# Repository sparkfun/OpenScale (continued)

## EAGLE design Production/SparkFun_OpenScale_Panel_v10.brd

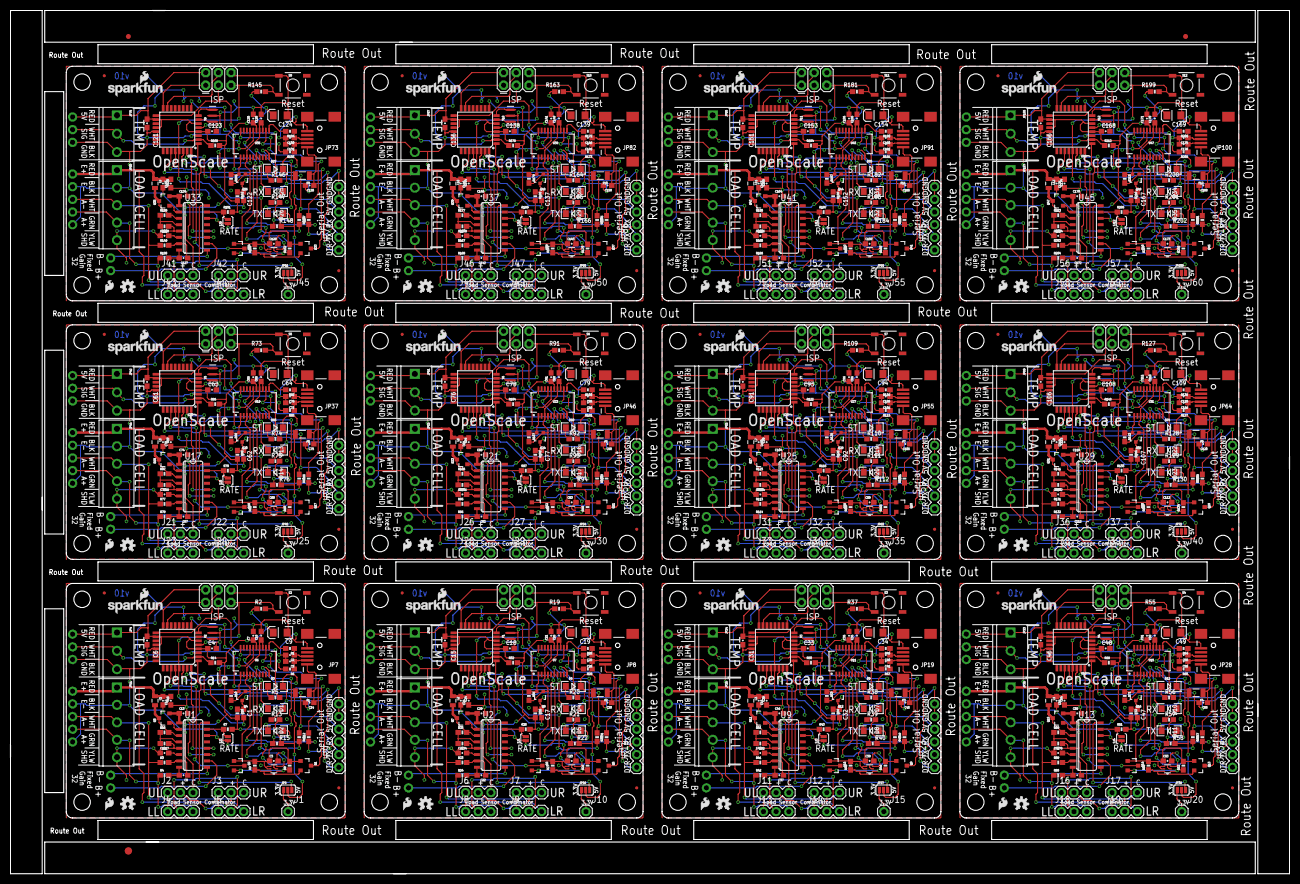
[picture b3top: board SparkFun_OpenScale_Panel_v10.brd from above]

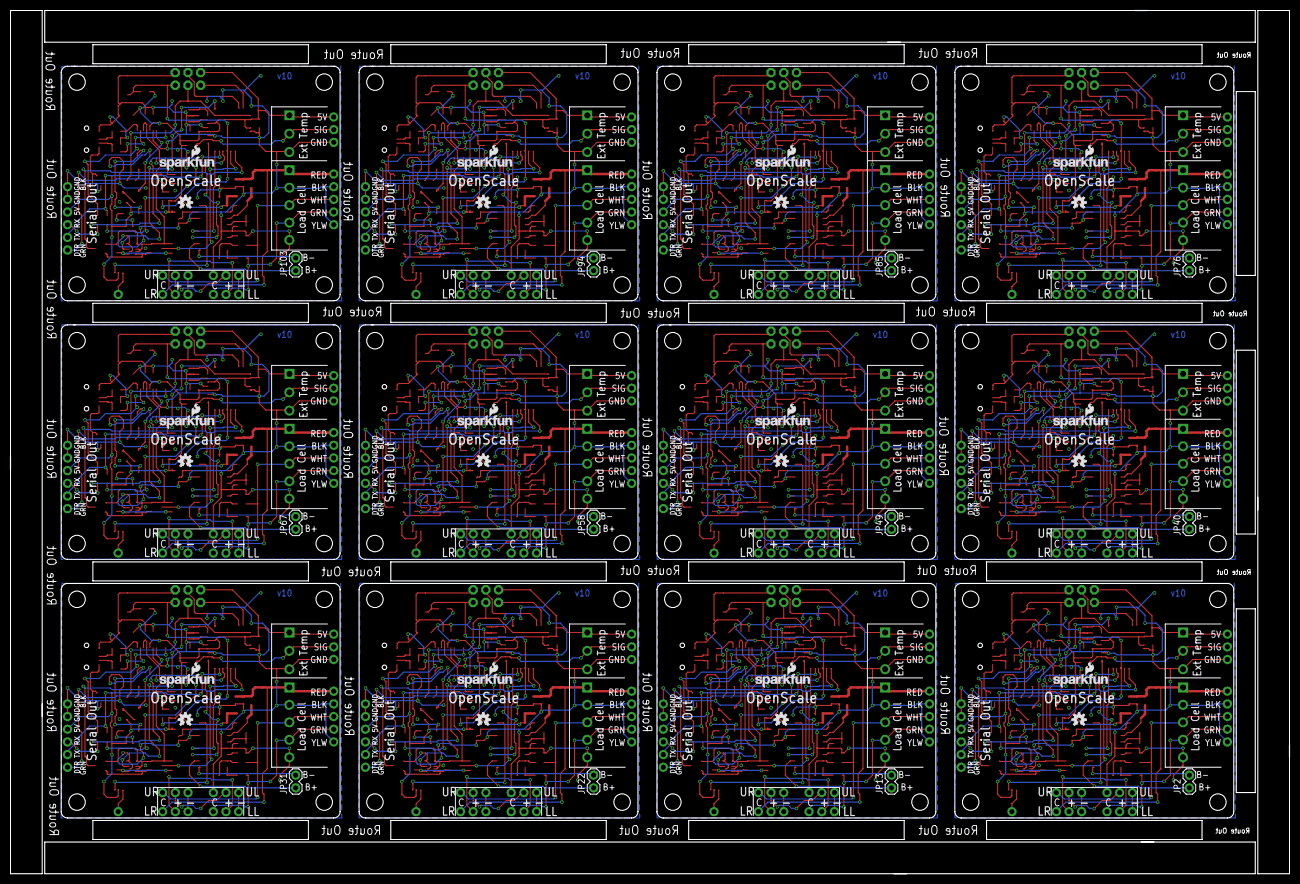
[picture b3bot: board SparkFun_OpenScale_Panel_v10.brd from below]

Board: 2 copper layers, 256.3 x 173.0 mm, 891 parts (48 on the bottom side), 612 nets.

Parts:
C1, C3, C6, C7, C8, C10, C11, C14, C15, C16, C17, C20, C21, C22, C23, C24, C27, C30, C31, C32, C35, C36, C37, C38, C39, C42, C45, C46, C47, C50, C51, C52, C53, C54, C57, C60, C61, C62, C65, C66, C67, C68, C69, C72, C75, C76, C77, C80, C81, C82, C83, C84, C87, C90, C91, C92, C95, C96, C97, C98, C99, C102, C105, C106, C107, C110, C111, C112, C113, C114, C117, C120, C121, C122, C125, C126, C127, C128, C129, C132, C135, C136, C137, C140, C141, C142, C143, C144, C147, C150, C151, C152, C155, C156, C157, C158, C159, C162, C165, C166, C167, C170, C171, C172, C173, C174, C177, C180: 0.1uF; 0603-CAP
C2, C5, C25, C26, C40, C41, C55, C56, C70, C71, C85, C86, C100, C101, C115, C116, C130, C131, C145, C146, C160, C161, C175, C176: 47pF; 0603-CAP
C4, C12, C13, C18, C28, C29, C33, C43, C44, C48, C58, C59, C63, C73, C74, C78, C88, C89, C93, C103, C104, C108, C118, C119, C123, C133, C134, C138, C148, C149, C153, C163, C164, C168, C178, C179: 1.0uF; 0603-CAP
C9, C19, C34, C49, C64, C79, C94, C109, C124, C139, C154, C169: 10uF; EIA3216
D1, D4, D7, D10, D13, D16, D19, D22, D25, D28, D31, D34: Yellow; LED-1206
D2, D5, D8, D11, D14, D17, D20, D23, D26, D29, D32, D35: GREEN; LED-1206
D3, D6, D9, D12, D15, D18, D21, D24, D27, D30, D33, D36: BLUE; LED-1206
E$1: FIDUCIAL-1.5X3
E$7, E$8: FIDUCIAL-1X2
F1, F2, F3, F4, F5, F6, F7, F8, F9, F10, F11, F12: PTCSMD; PTC-1206
FID1, FID2, FID3, FID4, FID5, FID6, FID7, FID8, FID9, FID10, FID11, FID12, FID13, FID14, FID15, FID16, FID17, FID18, FID19, FID20, FID21, FID22, FID23, FID24: FIDUCIALUFIDUCIAL; MICRO-FIDUCIAL
J1, J10, J15, J20, J25, J30, J35, J40, J45, J50, J55, J60: 3.3V; 1X01
J2, J6, J11, J16, J21, J26, J31, J36, J41, J46, J51, J56: UL; 1X03
J3, J7, J12, J17, J22, J27, J32, J37, J42, J47, J52, J57: UR; 1X03
J4, J8, J13, J18, J23, J28, J33, J38, J43, J48, J53, J58: LL; 1X03
J5, J9, J14, J19, J24, J29, J34, J39, J44, J49, J54, J59: LR; 1X03
JP1, JP12, JP21, JP30, JP39, JP48, JP57, JP66, JP75, JP84, JP93, JP102: Temp; 1X03_NO_SILK
JP2, JP13, JP22, JP31, JP40, JP49, JP58, JP67, JP76, JP85, JP94, JP103: Fixed Gain 32; 1X02
JP3, JP16, JP25, JP34, JP43, JP52, JP61, JP70, JP79, JP88, JP97, JP106: Load; 1X05_NO_SILK
JP4, JP15, JP24, JP33, JP42, JP51, JP60, JP69, JP78, JP87, JP96, JP105: Screw; SCREWTERMINAL-3.5MM-3_LOCK.007S
JP5, JP10, JP20, JP29, JP38, JP47, JP56, JP65, JP74, JP83, JP92, JP101: AVR_PRG; 2X3
JP6, JP18, JP27, JP36, JP45, JP54, JP63, JP72, JP81, JP90, JP99, JP108: JUMPER-PAD-3-2OF3_NC_BY_PASTE; PAD-JUMPER-3-2OF3_NC_BY_PASTE_YES_SILK_FULL_BOX
JP7, JP8, JP19, JP28, JP37, JP46, JP55, JP64, JP73, JP82, JP91, JP100: USBSMD; USB-MINIB
JP9, JP14, JP23, JP32, JP41, JP50, JP59, JP68, JP77, JP86, JP95, JP104: FTDI_BASIC
JP11, JP17, JP26, JP35, JP44, JP53, JP62, JP71, JP80, JP89, JP98, JP107: Screw Terminals; SCREWTERMINAL-3.5MM-5
L1, L2, L3, L4, L5, L6, L7, L8, L9, L10, L11, L12: 3.3uH; 0805
LOGO1, LOGO4, LOGO7, LOGO9, LOGO12, LOGO14, LOGO17, LOGO19, LOGO22, LOGO24, LOGO27, LOGO29, LOGO32, LOGO34, LOGO37, LOGO39, LOGO42, LOGO44, LOGO47, LOGO49, LOGO52, LOGO54, LOGO57, LOGO59: SFE_LOGO_NAME_FLAME.1_INCH; SFE_LOGO_NAME_FLAME_.1
LOGO2, LOGO5, LOGO6, LOGO10, LOGO11, LOGO15, LOGO16, LOGO20, LOGO21, LOGO25, LOGO26, LOGO30, LOGO31, LOGO35, LOGO36, LOGO40, LOGO41, LOGO45, LOGO46, LOGO50, LOGO51, LOGO55, LOGO56, LOGO60: OSHW-LOGOS; OSHW-LOGO-S
LOGO3, LOGO8, LOGO13, LOGO18, LOGO23, LOGO28, LOGO33, LOGO38, LOGO43, LOGO48, LOGO53, LOGO58: SFE_LOGO_FLAME.1_INCH; SFE_LOGO_FLAME_.1
Q1, Q2, Q5, Q6, Q9, Q10, Q13, Q14, Q17, Q18, Q21, Q22, Q25, Q26, Q29, Q30, Q33, Q34, Q37, Q38, Q41, Q42, Q45, Q46: 200mA/50V; SOT23-3
Q3, Q7, Q11, Q15, Q19, Q23, Q27, Q31, Q35, Q39, Q43, Q47: MMBT4403; SOT23-3
Q4, Q8, Q12, Q16, Q20, Q24, Q28, Q32, Q36, Q40, Q44, Q48: MOSFET-NCHANNEL2N7002PW; SOT323
R1, R6, R28, R29, R46, R47, R64, R65, R82, R83, R100, R101, R118, R119, R136, R137, R154, R155, R172, R173, R190, R191, R208, R209: 27; 0603
R2, R7, R10, R18, R19, R25, R35, R36, R37, R43, R53, R54, R55, R61, R71, R72, R73, R79, R89, R90, R91, R97, R107, R108, R109, R115, R125, R126, R127, R133, R143, R144, R145, R151, R161, R162, R163, R169, R179, R180, R181, R187, R197, R198, R199, R205, R215, R216: 10K; 0603-RES
R3, R4, R23, R24, R41, R42, R59, R60, R77, R78, R95, R96, R113, R114, R131, R132, R149, R150, R167, R168, R185, R186, R203, R204: 100; 0603-RES
R5, R11, R12, R13, R15, R20, R21, R22, R30, R31, R38, R39, R40, R48, R49, R56, R57, R58, R66, R67, R74, R75, R76, R84, R85, R92, R93, R94, R102, R103, R110, R111, R112, R120, R121, R128, R129, R130, R138, R139, R146, R147, R148, R156, R157, R164, R165, R166, R174, R175, R182, R183, R184, R192, R193, R200, R201, R202, R210, R211: 1K; 0603-RES
R8, R9, R14, R26, R27, R32, R44, R45, R50, R62, R63, R68, R80, R81, R86, R98, R99, R104, R116, R117, R122, R134, R135, R140, R152, R153, R158, R170, R171, R176, R188, R189, R194, R206, R207, R212: 4.7K; 0603-RES
R16, R33, R51, R69, R87, R105, R123, R141, R159, R177, R195, R213: 20k; 0603-RES
R17, R34, R52, R70, R88, R106, R124, R142, R160, R178, R196, R214: 8.2K; 0603-RES
S1, S2, S3, S4, S5, S6, S7, S8, S9, S10, S11, S12: Reset; TACTILE-SWITCH-SMD
SJ1, SJ2, SJ3, SJ4, SJ5, SJ6, SJ7, SJ8, SJ9, SJ10, SJ11, SJ12: JUMPER-PAD-2-NC_BY_PASTE; PAD-JUMPER-2-NC_BY_PASTE_YES_SILK
STANDOFF1, STANDOFF2, STANDOFF3, STANDOFF4, STANDOFF5, STANDOFF6, STANDOFF7, STANDOFF8, STANDOFF9, STANDOFF10, STANDOFF11, STANDOFF12, STANDOFF13, STANDOFF14, STANDOFF15, STANDOFF16, STANDOFF17, STANDOFF18, STANDOFF19, STANDOFF20, STANDOFF21, STANDOFF22, STANDOFF23, STANDOFF24, STANDOFF25, STANDOFF26, STANDOFF27, STANDOFF28, STANDOFF29, STANDOFF30, STANDOFF31, STANDOFF32, STANDOFF33, STANDOFF34, STANDOFF35, STANDOFF36, STANDOFF37, STANDOFF38, STANDOFF39, STANDOFF40, STANDOFF41, STANDOFF42, STANDOFF43, STANDOFF44, STANDOFF45, STANDOFF46, STANDOFF47, STANDOFF48: STAND-OFF
U1, U2, U9, U13, U17, U21, U25, U29, U33, U37, U41, U45: HX711; SO16
U3, U5, U10, U14, U18, U22, U26, U30, U34, U38, U42, U46: TMP102; SOT563
U4, U8, U12, U16, U20, U24, U28, U32, U36, U40, U44, U48: ATMEGA328P_TQFP; TQFP32-08
U6, U7, U11, U15, U19, U23, U27, U31, U35, U39, U43, U47: FT231XS; SSOP20_L
Y1, Y2, Y3, Y4, Y5, Y6, Y7, Y8, Y9, Y10, Y11, Y12: 16MHZ; RESONATOR-SMD

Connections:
1: J8.2, J9.2
2: J4.2, J5.2
3: J13.2, J14.2
3.3V: C3.1, C10.1, Q1.1, Q2.1, Q4.1, R8.2, R9.2, R10.2, U3.4, U3.5, U6.3, U6.13, U6.14
3.3V1: C20.1, C23.1, Q5.1, Q6.1, Q8.1, R26.2, R27.2, R35.2, U5.4, U5.5, U7.3, U7.13, U7.14
3.3V2: C35.1, C38.1, Q9.1, Q10.1, Q12.1, R44.2, R45.2, R53.2, U10.4, U10.5, U11.3, U11.13, U11.14
3.3V3: C50.1, C53.1, Q13.1, Q14.1, Q16.1, R62.2, R63.2, R71.2, U14.4, U14.5, U15.3, U15.13, U15.14
3.3V4: C65.1, C68.1, Q17.1, Q18.1, Q20.1, R80.2, R81.2, R89.2, U18.4, U18.5, U19.3, U19.13, U19.14
3.3V5: C80.1, C83.1, Q21.1, Q22.1, Q24.1, R98.2, R99.2, R107.2, U22.4, U22.5, U23.3, U23.13, U23.14
3.3V6: C95.1, C98.1, Q25.1, Q26.1, Q28.1, R116.2, R117.2, R125.2, U26.4, U26.5, U27.3, U27.13, U27.14
3.3V7: C110.1, C113.1, Q29.1, Q30.1, Q32.1, R134.2, R135.2, R143.2, U30.4, U30.5, U31.3, U31.13, U31.14
3.3V8: C125.1, C128.1, Q33.1, Q34.1, Q36.1, R152.2, R153.2, R161.2, U34.4, U34.5, U35.3, U35.13, U35.14
3.3V9: C140.1, C143.1, Q37.1, Q38.1, Q40.1, R170.2, R171.2, R179.2, U38.4, U38.5, U39.3, U39.13, U39.14
3.3V10: C155.1, C158.1, Q41.1, Q42.1, Q44.1, R188.2, R189.2, R197.2, U42.4, U42.5, U43.3, U43.13, U43.14
3.3V11: C170.1, C173.1, Q45.1, Q46.1, Q48.1, R206.2, R207.2, R215.2, U46.4, U46.5, U47.3, U47.13, U47.14
4: J18.2, J19.2
5: J23.2, J24.2
5V: C4.1, C6.1, C7.1, C9.A, C13.1, F1.2, JP1.1, JP4.1, JP5.2, JP6.2, JP9.VCC, Q3.2, R2.2, R7.2, R13.2, R14.2, R15.2, R18.2, U1.1, U4.4, U4.6, U4.18, U4.20, U6.15
5V1: C15.1, C18.1, C19.A, C21.1, C29.1, F2.2, JP10.2, JP12.1, JP14.VCC, JP15.1, JP18.2, Q7.2, R19.2, R21.2, R22.2, R25.2, R32.2, R36.2, U2.1, U7.15, U8.4, U8.6, U8.18, U8.20
5V2: C31.1, C33.1, C34.A, C36.1, C44.1, F3.2, JP20.2, JP21.1, JP23.VCC, JP24.1, JP27.2, Q11.2, R37.2, R39.2, R40.2, R43.2, R50.2, R54.2, U9.1, U11.15, U12.4, U12.6, U12.18, U12.20
5V3: C46.1, C48.1, C49.A, C51.1, C59.1, F4.2, JP29.2, JP30.1, JP32.VCC, JP33.1, JP36.2, Q15.2, R55.2, R57.2, R58.2, R61.2, R68.2, R72.2, U13.1, U15.15, U16.4, U16.6, U16.18, U16.20
5V4: C61.1, C63.1, C64.A, C66.1, C74.1, F5.2, JP38.2, JP39.1, JP41.VCC, JP42.1, JP45.2, Q19.2, R73.2, R75.2, R76.2, R79.2, R86.2, R90.2, U17.1, U19.15, U20.4, U20.6, U20.18, U20.20
5V5: C76.1, C78.1, C79.A, C81.1, C89.1, F6.2, JP47.2, JP48.1, JP50.VCC, JP51.1, JP54.2, Q23.2, R91.2, R93.2, R94.2, R97.2, R104.2, R108.2, U21.1, U23.15, U24.4, U24.6, U24.18, U24.20
5V6: C91.1, C93.1, C94.A, C96.1, C104.1, F7.2, JP56.2, JP57.1, JP59.VCC, JP60.1, JP63.2, Q27.2, R109.2, R111.2, R112.2, R115.2, R122.2, R126.2, U25.1, U27.15, U28.4, U28.6, U28.18, U28.20
5V7: C106.1, C108.1, C109.A, C111.1, C119.1, F8.2, JP65.2, JP66.1, JP68.VCC, JP69.1, JP72.2, Q31.2, R127.2, R129.2, R130.2, R133.2, R140.2, R144.2, U29.1, U31.15, U32.4, U32.6, U32.18, U32.20
5V8: C121.1, C123.1, C124.A, C126.1, C134.1, F9.2, JP74.2, JP75.1, JP77.VCC, JP78.1, JP81.2, Q35.2, R145.2, R147.2, R148.2, R151.2, R158.2, R162.2, U33.1, U35.15, U36.4, U36.6, U36.18, U36.20
5V9: C136.1, C138.1, C139.A, C141.1, C149.1, F10.2, JP83.2, JP84.1, JP86.VCC, JP87.1, JP90.2, Q39.2, R163.2, R165.2, R166.2, R169.2, R176.2, R180.2, U37.1, U39.15, U40.4, U40.6, U40.18, U40.20
5V10: C151.1, C153.1, C154.A, C156.1, C164.1, F11.2, JP92.2, JP93.1, JP95.VCC, JP96.1, JP99.2, Q43.2, R181.2, R183.2, R184.2, R187.2, R194.2, R198.2, U41.1, U43.15, U44.4, U44.6, U44.18, U44.20
5V11: C166.1, C168.1, C169.A, C171.1, C179.1, F12.2, JP101.2, JP102.1, JP104.VCC, JP105.1, JP108.2, Q47.2, R199.2, R201.2, R202.2, R205.2, R212.2, R216.2, U45.1, U47.15, U48.4, U48.6, U48.18, U48.20
6: J28.2, J29.2
7: J33.2, J34.2
8: J38.2, J39.2
9: J43.2, J44.2
10: J48.2, J49.2
11: J53.2, J54.2
12: J58.2, J59.2
A+: J4.3, JP3.2, JP11.4, R4.1
A+1: J8.3, JP16.2, JP17.4, R24.1
A+2: J13.3, JP25.2, JP26.4, R42.1
A+3: J18.3, JP34.2, JP35.4, R60.1
A+4: J23.3, JP43.2, JP44.4, R78.1
A+5: J28.3, JP52.2, JP53.4, R96.1
A+6: J33.3, JP61.2, JP62.4, R114.1
A+7: J38.3, JP70.2, JP71.4, R132.1
A+8: J43.3, JP79.2, JP80.4, R150.1
A+9: J48.3, JP88.2, JP89.4, R168.1
A+10: J53.3, JP97.2, JP98.4, R186.1
A+11: J58.3, JP106.2, JP107.4, R204.1
A-: J3.3, JP3.3, JP11.3, R3.1
A-1: J7.3, JP16.3, JP17.3, R23.1
A-2: J12.3, JP25.3, JP26.3, R41.1
A-3: J17.3, JP34.3, JP35.3, R59.1
A-4: J22.3, JP43.3, JP44.3, R77.1
A-5: J27.3, JP52.3, JP53.3, R95.1
A-6: J32.3, JP61.3, JP62.3, R113.1
A-7: J37.3, JP70.3, JP71.3, R131.1
A-8: J42.3, JP79.3, JP80.3, R149.1
A-9: J47.3, JP88.3, JP89.3, R167.1
A-10: J52.3, JP97.3, JP98.3, R185.1
A-11: J57.3, JP106.3, JP107.3, R203.1
ALERT: U3.3, U4.9
ALERT1: U5.3, U8.9
ALERT2: U10.3, U12.9
ALERT3: U14.3, U16.9
ALERT4: U18.3, U20.9
ALERT5: U22.3, U24.9
ALERT6: U26.3, U28.9
ALERT7: U30.3, U32.9
ALERT8: U34.3, U36.9
ALERT9: U38.3, U40.9
ALERT10: U42.3, U44.9
ALERT11: U46.3, U48.9
AVDD: C12.2, C16.1, J5.3, JP3.5, JP11.1, L1.1
AVDD1: C24.1, C28.2, J9.3, JP16.5, JP17.1, L2.1
AVDD2: C39.1, C43.2, J14.3, JP25.5, JP26.1, L3.1
AVDD3: C54.1, C58.2, J19.3, JP34.5, JP35.1, L4.1
AVDD4: C69.1, C73.2, J24.3, JP43.5, JP44.1, L5.1
AVDD5: C84.1, C88.2, J29.3, JP52.5, JP53.1, L6.1
AVDD6: C99.1, C103.2, J34.3, JP61.5, JP62.1, L7.1
AVDD7: C114.1, C118.2, J39.3, JP70.5, JP71.1, L8.1
AVDD8: C129.1, C133.2, J44.3, JP79.5, JP80.1, L9.1
AVDD9: C144.1, C148.2, J49.3, JP88.5, JP89.1, L10.1
AVDD10: C159.1, C163.2, J54.3, JP97.5, JP98.1, L11.1
AVDD11: C174.1, C178.2, J59.3, JP106.5, JP107.1, L12.1
B+: JP2.1, U1.10
B+1: JP13.1, U2.10
B+2: JP22.1, U9.10
B+3: JP31.1, U13.10
B+4: JP40.1, U17.10
B+5: JP49.1, U21.10
B+6: JP58.1, U25.10
B+7: JP67.1, U29.10
B+8: JP76.1, U33.10
B+9: JP85.1, U37.10
B+10: JP94.1, U41.10
B+11: JP103.1, U45.10
B-: JP2.2, U1.9
B-1: JP13.2, U2.9
B-2: JP22.2, U9.9
B-3: JP31.2, U13.9
B-4: JP40.2, U17.9
B-5: JP49.2, U21.9
B-6: JP58.2, U25.9
B-7: JP67.2, U29.9
B-8: JP76.2, U33.9
B-9: JP85.2, U37.9
B-10: JP94.2, U41.9
B-11: JP103.2, U45.9
D1: JP10.4, U8.15
D2: JP10.1, U8.16
D3: JP10.3, R20.2, U8.17
D4: JP20.4, U12.15
D5: JP20.1, U12.16
D6: JP20.3, R38.2, U12.17
D7: JP29.4, U16.15
D8: JP29.1, U16.16
D9: JP29.3, R56.2, U16.17
D10: JP38.4, U20.15
D11: JP5.4, U4.15
D12: JP5.1, U4.16
D13: JP5.3, R5.2, U4.17
D14: JP38.1, U20.16
D15: JP38.3, R74.2, U20.17
D16: JP47.4, U24.15
D17: JP47.1, U24.16
D18: JP47.3, R92.2, U24.17
D19: JP56.4, U28.15
D20: JP56.1, U28.16
D21: JP56.3, R110.2, U28.17
D22: JP65.4, U32.15
D23: JP65.1, U32.16
D24: JP65.3, R128.2, U32.17
D25: JP74.4, U36.15
D26: JP74.1, U36.16
D27: JP74.3, R146.2, U36.17
D28: JP83.4, U40.15
D29: JP83.1, U40.16
D30: JP83.3, R164.2, U40.17
D31: JP92.4, U44.15
D32: JP92.1, U44.16
D33: JP92.3, R182.2, U44.17
D34: JP101.4, U48.15
D35: JP101.1, U48.16
D36: JP101.3, R200.2, U48.17
DTR: C1.1, JP9.DTR, Q4.3, R18.1
DTR1: C17.1, JP14.DTR, Q8.3, R36.1
DTR2: C32.1, JP23.DTR, Q12.3, R54.1
DTR3: C47.1, JP32.DTR, Q16.3, R72.1
DTR4: C62.1, JP41.DTR, Q20.3, R90.1
DTR5: C77.1, JP50.DTR, Q24.3, R108.1
DTR6: C92.1, JP59.DTR, Q28.3, R126.1
DTR7: C107.1, JP68.DTR, Q32.3, R144.1
DTR8: C122.1, JP77.DTR, Q36.3, R162.1
DTR9: C137.1, JP86.DTR, Q40.3, R180.1
DTR10: C152.1, JP95.DTR, Q44.3, R198.1
DTR11: C167.1, JP104.DTR, Q48.3, R216.1
GND: C2.2, C3.2, C4.2, C5.2, C6.2, C7.2, C9.C, C10.2, C11.1, C12.1, C13.2, C14.2, C16.2, D3.C, J2.3, JP1.3, JP3.1, JP3.4, JP4.3, JP5.6, JP7.GND, JP9.CTS, JP9.GND, JP11.2, JP11.5, R17.1, S2.1, SJ2.1, U1.5, U1.14, U3.2, U4.3, U4.5, U4.21, U6.6, U6.16, Y2.2
GND1: C15.2, C18.2, C19.C, C20.2, C21.2, C23.2, C24.2, C25.2, C26.2, C27.1, C28.1, C29.2, C30.2, D6.C, J6.3, JP8.GND, JP10.6, JP12.3, JP14.CTS, JP14.GND, JP15.3, JP16.1, JP16.4, JP17.2, JP17.5, R34.1, S1.1, SJ1.1, U2.5, U2.14, U5.2, U7.6, U7.16, U8.3, U8.5, U8.21, Y1.2
GND2: C31.2, C33.2, C34.C, C35.2, C36.2, C38.2, C39.2, C40.2, C41.2, C42.1, C43.1, C44.2, C45.2, D9.C, J11.3, JP19.GND, JP20.6, JP21.3, JP23.CTS, JP23.GND, JP24.3, JP25.1, JP25.4, JP26.2, JP26.5, R52.1, S3.1, SJ3.1, U9.5, U9.14, U10.2, U11.6, U11.16, U12.3, U12.5, U12.21, Y3.2
GND3: C46.2, C48.2, C49.C, C50.2, C51.2, C53.2, C54.2, C55.2, C56.2, C57.1, C58.1, C59.2, C60.2, D12.C, J16.3, JP28.GND, JP29.6, JP30.3, JP32.CTS, JP32.GND, JP33.3, JP34.1, JP34.4, JP35.2, JP35.5, R70.1, S4.1, SJ4.1, U13.5, U13.14, U14.2, U15.6, U15.16, U16.3, U16.5, U16.21, Y4.2
GND4: C61.2, C63.2, C64.C, C65.2, C66.2, C68.2, C69.2, C70.2, C71.2, C72.1, C73.1, C74.2, C75.2, D15.C, J21.3, JP37.GND, JP38.6, JP39.3, JP41.CTS, JP41.GND, JP42.3, JP43.1, JP43.4, JP44.2, JP44.5, R88.1, S5.1, SJ5.1, U17.5, U17.14, U18.2, U19.6, U19.16, U20.3, U20.5, U20.21, Y5.2
GND5: C76.2, C78.2, C79.C, C80.2, C81.2, C83.2, C84.2, C85.2, C86.2, C87.1, C88.1, C89.2, C90.2, D18.C, J26.3, JP46.GND, JP47.6, JP48.3, JP50.CTS, JP50.GND, JP51.3, JP52.1, JP52.4, JP53.2, JP53.5, R106.1, S6.1, SJ6.1, U21.5, U21.14, U22.2, U23.6, U23.16, U24.3, U24.5, U24.21, Y6.2
GND6: C91.2, C93.2, C94.C, C95.2, C96.2, C98.2, C99.2, C100.2, C101.2, C102.1, C103.1, C104.2, C105.2, D21.C, J31.3, JP55.GND, JP56.6, JP57.3, JP59.CTS, JP59.GND, JP60.3, JP61.1, JP61.4, JP62.2, JP62.5, R124.1, S7.1, SJ7.1, U25.5, U25.14, U26.2, U27.6, U27.16, U28.3, U28.5, U28.21, Y7.2
GND7: C106.2, C108.2, C109.C, C110.2, C111.2, C113.2, C114.2, C115.2, C116.2, C117.1, C118.1, C119.2, C120.2, D24.C, J36.3, JP64.GND, JP65.6, JP66.3, JP68.CTS, JP68.GND, JP69.3, JP70.1, JP70.4, JP71.2, JP71.5, R142.1, S8.1, SJ8.1, U29.5, U29.14, U30.2, U31.6, U31.16, U32.3, U32.5, U32.21, Y8.2
GND8: C121.2, C123.2, C124.C, C125.2, C126.2, C128.2, C129.2, C130.2, C131.2, C132.1, C133.1, C134.2, C135.2, D27.C, J41.3, JP73.GND, JP74.6, JP75.3, JP77.CTS, JP77.GND, JP78.3, JP79.1, JP79.4, JP80.2, JP80.5, R160.1, S9.1, SJ9.1, U33.5, U33.14, U34.2, U35.6, U35.16, U36.3, U36.5, U36.21, Y9.2
GND9: C136.2, C138.2, C139.C, C140.2, C141.2, C143.2, C144.2, C145.2, C146.2, C147.1, C148.1, C149.2, C150.2, D30.C, J46.3, JP82.GND, JP83.6, JP84.3, JP86.CTS, JP86.GND, JP87.3, JP88.1, JP88.4, JP89.2, JP89.5, R178.1, S10.1, SJ10.1, U37.5, U37.14, U38.2, U39.6, U39.16, U40.3, U40.5, U40.21, Y10.2
GND10: C151.2, C153.2, C154.C, C155.2, C156.2, C158.2, C159.2, C160.2, C161.2, C162.1, C163.1, C164.2, C165.2, D33.C, J51.3, JP91.GND, JP92.6, JP93.3, JP95.CTS, JP95.GND, JP96.3, JP97.1, JP97.4, JP98.2, JP98.5, R196.1, S11.1, SJ11.1, U41.5, U41.14, U42.2, U43.6, U43.16, U44.3, U44.5, U44.21, Y11.2
GND11: C166.2, C168.2, C169.C, C170.2, C171.2, C173.2, C174.2, C175.2, C176.2, C177.1, C178.1, C179.2, C180.2, D36.C, J56.3, JP100.GND, JP101.6, JP102.3, JP104.CTS, JP104.GND, JP105.3, JP106.1, JP106.4, JP107.2, JP107.5, R214.1, S12.1, SJ12.1, U45.5, U45.14, U46.2, U47.6, U47.16, U48.3, U48.5, U48.21, Y12.2
LC_DOUT: U1.12, U4.32
LC_DOUT1: U2.12, U8.32
LC_DOUT2: U9.12, U12.32
LC_DOUT3: U13.12, U16.32
LC_DOUT4: U17.12, U20.32
LC_DOUT5: U21.12, U24.32
LC_DOUT6: U25.12, U28.32
LC_DOUT7: U29.12, U32.32
LC_DOUT8: U33.12, U36.32
LC_DOUT9: U37.12, U40.32
LC_DOUT10: U41.12, U44.32
LC_DOUT11: U45.12, U48.32
LC_SCK: U1.11, U4.1
LC_SCK1: U2.11, U8.1
LC_SCK2: U9.11, U12.1
LC_SCK3: U13.11, U16.1
LC_SCK4: U17.11, U20.1
LC_SCK5: U21.11, U24.1
LC_SCK6: U25.11, U28.1
LC_SCK7: U29.11, U32.1
LC_SCK8: U33.11, U36.1
LC_SCK9: U37.11, U40.1
LC_SCK10: U41.11, U44.1
LC_SCK11: U45.11, U48.1
LV_SCL: Q2.2, R8.1, U3.1
LV_SCL1: Q6.2, R26.1, U5.1
LV_SCL2: Q10.2, R44.1, U10.1
LV_SCL3: Q14.2, R62.1, U14.1
LV_SCL4: Q18.2, R80.1, U18.1
LV_SCL5: Q22.2, R98.1, U22.1
LV_SCL6: Q26.2, R116.1, U26.1
LV_SCL7: Q30.2, R134.1, U30.1
LV_SCL8: Q34.2, R152.1, U34.1
LV_SCL9: Q38.2, R170.1, U38.1
LV_SCL10: Q42.2, R188.1, U42.1
LV_SCL11: Q46.2, R206.1, U46.1
LV_SDA: Q1.2, R9.1, U3.6
LV_SDA1: Q5.2, R27.1, U5.6
LV_SDA2: Q9.2, R45.1, U10.6
LV_SDA3: Q13.2, R63.1, U14.6
LV_SDA4: Q17.2, R81.1, U18.6
LV_SDA5: Q21.2, R99.1, U22.6
LV_SDA6: Q25.2, R117.1, U26.6
LV_SDA7: Q29.2, R135.1, U30.6
LV_SDA8: Q33.2, R153.1, U34.6
LV_SDA9: Q37.2, R171.1, U38.6
LV_SDA10: Q41.2, R189.1, U42.6
LV_SDA11: Q45.2, R207.1, U46.6
unnamed: U4.7, Y2.1
unnamed: D3.A, R5.1
unnamed: U4.8, Y2.3
unnamed: C5.1, JP7.D-, R6.1
unnamed: D1.A, R13.1
unnamed: D2.A, R15.1
unnamed: C2.1, JP7.D+, R1.1
unnamed: R6.2, U6.12
unnamed: R7.1, SJ2.2, U1.15
unnamed: C8.1, R3.2, U1.7
unnamed: C8.2, R4.2, U1.8
unnamed: C14.1, F1.1, JP7.VBUS
unnamed: R1.2, U6.11
unnamed: R12.2, U6.4
unnamed: JP6.3, U1.16
unnamed: R11.2, U6.20
unnamed: Q3.1, U1.2
unnamed: R16.1, R17.2, U1.4
unnamed: J1.1, JP6.1
unnamed: J2.2, J3.2
unnamed: C11.2, U1.6
unnamed: J2.1, J4.1
unnamed: J3.1, J5.1
unnamed: Q4.2, R10.1, U6.1
unnamed: D6.A, R20.1
unnamed: U8.7, Y1.1
unnamed: U8.8, Y1.3
unnamed: D4.A, R21.1
unnamed: D5.A, R22.1
unnamed: R25.1, SJ1.2, U2.15
unnamed: C22.1, R23.2, U2.7
unnamed: C22.2, R24.2, U2.8
unnamed: C30.1, F2.1, JP8.VBUS
unnamed: C26.1, JP8.D-, R29.1
unnamed: C25.1, JP8.D+, R28.1
unnamed: R29.2, U7.12
unnamed: R28.2, U7.11
unnamed: R30.2, U7.20
unnamed: Q7.1, U2.2
unnamed: R33.1, R34.2, U2.4
unnamed: C27.2, U2.6
unnamed: J6.2, J7.2
unnamed: J6.1, J8.1
unnamed: J7.1, J9.1
unnamed: J10.1, JP18.1
unnamed: JP18.3, U2.16
unnamed: R31.2, U7.4
unnamed: Q8.2, R35.1, U7.1
unnamed: D9.A, R38.1
unnamed: U12.7, Y3.1
unnamed: U12.8, Y3.3
unnamed: D7.A, R39.1
unnamed: D8.A, R40.1
unnamed: R43.1, SJ3.2, U9.15
unnamed: C37.1, R41.2, U9.7
unnamed: C37.2, R42.2, U9.8
unnamed: C45.1, F3.1, JP19.VBUS
unnamed: C41.1, JP19.D-, R47.1
unnamed: C40.1, JP19.D+, R46.1
unnamed: R47.2, U11.12
unnamed: R46.2, U11.11
unnamed: R48.2, U11.20
unnamed: Q11.1, U9.2
unnamed: R51.1, R52.2, U9.4
unnamed: C42.2, U9.6
unnamed: J11.2, J12.2
unnamed: J11.1, J13.1
unnamed: J12.1, J14.1
unnamed: J15.1, JP27.1
unnamed: JP27.3, U9.16
unnamed: R49.2, U11.4
unnamed: Q12.2, R53.1, U11.1
unnamed: D12.A, R56.1
unnamed: U16.7, Y4.1
unnamed: U16.8, Y4.3
unnamed: D10.A, R57.1
unnamed: D11.A, R58.1
unnamed: R61.1, SJ4.2, U13.15
unnamed: C52.1, R59.2, U13.7
unnamed: C52.2, R60.2, U13.8
unnamed: C60.1, F4.1, JP28.VBUS
unnamed: C56.1, JP28.D-, R65.1
unnamed: C55.1, JP28.D+, R64.1
unnamed: R65.2, U15.12
unnamed: R64.2, U15.11
unnamed: R66.2, U15.20
unnamed: Q15.1, U13.2
unnamed: R69.1, R70.2, U13.4
unnamed: C57.2, U13.6
unnamed: J16.2, J17.2
unnamed: J16.1, J18.1
unnamed: J17.1, J19.1
unnamed: J20.1, JP36.1
unnamed: JP36.3, U13.16
unnamed: R67.2, U15.4
unnamed: Q16.2, R71.1, U15.1
unnamed: D15.A, R74.1
unnamed: U20.7, Y5.1
unnamed: U20.8, Y5.3
unnamed: D13.A, R75.1
unnamed: D14.A, R76.1
unnamed: R79.1, SJ5.2, U17.15
unnamed: C67.1, R77.2, U17.7
unnamed: C67.2, R78.2, U17.8
unnamed: C75.1, F5.1, JP37.VBUS
unnamed: C71.1, JP37.D-, R83.1
unnamed: C70.1, JP37.D+, R82.1
unnamed: R83.2, U19.12
unnamed: R82.2, U19.11
unnamed: R84.2, U19.20
unnamed: Q19.1, U17.2
unnamed: R87.1, R88.2, U17.4
unnamed: C72.2, U17.6
unnamed: J21.2, J22.2
unnamed: J21.1, J23.1
unnamed: J22.1, J24.1
unnamed: J25.1, JP45.1
unnamed: JP45.3, U17.16
unnamed: R85.2, U19.4
unnamed: Q20.2, R89.1, U19.1
unnamed: D18.A, R92.1
unnamed: U24.7, Y6.1
unnamed: U24.8, Y6.3
unnamed: D16.A, R93.1
unnamed: D17.A, R94.1
unnamed: R97.1, SJ6.2, U21.15
unnamed: C82.1, R95.2, U21.7
unnamed: C82.2, R96.2, U21.8
unnamed: C90.1, F6.1, JP46.VBUS
unnamed: C86.1, JP46.D-, R101.1
unnamed: C85.1, JP46.D+, R100.1
unnamed: R101.2, U23.12
unnamed: R100.2, U23.11
unnamed: R102.2, U23.20
unnamed: Q23.1, U21.2
unnamed: R105.1, R106.2, U21.4
unnamed: C87.2, U21.6
unnamed: J26.2, J27.2
unnamed: J26.1, J28.1
unnamed: J27.1, J29.1
unnamed: J30.1, JP54.1
unnamed: JP54.3, U21.16
unnamed: R103.2, U23.4
unnamed: Q24.2, R107.1, U23.1
unnamed: D21.A, R110.1
unnamed: U28.7, Y7.1
unnamed: U28.8, Y7.3
unnamed: D19.A, R111.1
unnamed: D20.A, R112.1
unnamed: R115.1, SJ7.2, U25.15
unnamed: C97.1, R113.2, U25.7
unnamed: C97.2, R114.2, U25.8
unnamed: C105.1, F7.1, JP55.VBUS
unnamed: C101.1, JP55.D-, R119.1
unnamed: C100.1, JP55.D+, R118.1
unnamed: R119.2, U27.12
unnamed: R118.2, U27.11
unnamed: R120.2, U27.20
unnamed: Q27.1, U25.2
unnamed: R123.1, R124.2, U25.4
unnamed: C102.2, U25.6
unnamed: J31.2, J32.2
unnamed: J31.1, J33.1
unnamed: J32.1, J34.1
unnamed: J35.1, JP63.1
unnamed: JP63.3, U25.16
unnamed: R121.2, U27.4
unnamed: Q28.2, R125.1, U27.1
unnamed: D24.A, R128.1
unnamed: U32.7, Y8.1
unnamed: U32.8, Y8.3
unnamed: D22.A, R129.1
unnamed: D23.A, R130.1
unnamed: R133.1, SJ8.2, U29.15
unnamed: C112.1, R131.2, U29.7
unnamed: C112.2, R132.2, U29.8
unnamed: C120.1, F8.1, JP64.VBUS
unnamed: C116.1, JP64.D-, R137.1
unnamed: C115.1, JP64.D+, R136.1
unnamed: R137.2, U31.12
unnamed: R136.2, U31.11
unnamed: R138.2, U31.20
unnamed: Q31.1, U29.2
unnamed: R141.1, R142.2, U29.4
unnamed: C117.2, U29.6
unnamed: J36.2, J37.2
unnamed: J36.1, J38.1
unnamed: J37.1, J39.1
unnamed: J40.1, JP72.1
unnamed: JP72.3, U29.16
unnamed: R139.2, U31.4
unnamed: Q32.2, R143.1, U31.1
unnamed: D27.A, R146.1
unnamed: U36.7, Y9.1
unnamed: U36.8, Y9.3
unnamed: D25.A, R147.1
unnamed: D26.A, R148.1
unnamed: R151.1, SJ9.2, U33.15
unnamed: C127.1, R149.2, U33.7
unnamed: C127.2, R150.2, U33.8
unnamed: C135.1, F9.1, JP73.VBUS
unnamed: C131.1, JP73.D-, R155.1
unnamed: C130.1, JP73.D+, R154.1
unnamed: R155.2, U35.12
unnamed: R154.2, U35.11
unnamed: R156.2, U35.20
unnamed: Q35.1, U33.2
unnamed: R159.1, R160.2, U33.4
unnamed: C132.2, U33.6
unnamed: J41.2, J42.2
unnamed: J41.1, J43.1
unnamed: J42.1, J44.1
unnamed: J45.1, JP81.1
unnamed: JP81.3, U33.16
unnamed: R157.2, U35.4
unnamed: Q36.2, R161.1, U35.1
unnamed: D30.A, R164.1
unnamed: U40.7, Y10.1
unnamed: U40.8, Y10.3
unnamed: D28.A, R165.1
unnamed: D29.A, R166.1
unnamed: R169.1, SJ10.2, U37.15
unnamed: C142.1, R167.2, U37.7
unnamed: C142.2, R168.2, U37.8
unnamed: C150.1, F10.1, JP82.VBUS
unnamed: C146.1, JP82.D-, R173.1
unnamed: C145.1, JP82.D+, R172.1
unnamed: R173.2, U39.12
unnamed: R172.2, U39.11
unnamed: R174.2, U39.20
unnamed: Q39.1, U37.2
unnamed: R177.1, R178.2, U37.4
unnamed: C147.2, U37.6
unnamed: J46.2, J47.2
unnamed: J46.1, J48.1
unnamed: J47.1, J49.1
unnamed: J50.1, JP90.1
unnamed: JP90.3, U37.16
unnamed: R175.2, U39.4
unnamed: Q40.2, R179.1, U39.1
unnamed: D33.A, R182.1
unnamed: U44.7, Y11.1
unnamed: U44.8, Y11.3
unnamed: D31.A, R183.1
unnamed: D32.A, R184.1
unnamed: R187.1, SJ11.2, U41.15
unnamed: C157.1, R185.2, U41.7
unnamed: C157.2, R186.2, U41.8
unnamed: C165.1, F11.1, JP91.VBUS
unnamed: C161.1, JP91.D-, R191.1
unnamed: C160.1, JP91.D+, R190.1
unnamed: R191.2, U43.12
unnamed: R190.2, U43.11
unnamed: R192.2, U43.20
unnamed: Q43.1, U41.2
unnamed: R195.1, R196.2, U41.4
unnamed: C162.2, U41.6
unnamed: J51.2, J52.2
unnamed: J51.1, J53.1
unnamed: J52.1, J54.1
unnamed: J55.1, JP99.1
unnamed: JP99.3, U41.16
unnamed: R193.2, U43.4
unnamed: Q44.2, R197.1, U43.1
unnamed: D36.A, R200.1
unnamed: U48.7, Y12.1
unnamed: U48.8, Y12.3
unnamed: D34.A, R201.1
unnamed: D35.A, R202.1
unnamed: R205.1, SJ12.2, U45.15
unnamed: C172.1, R203.2, U45.7
unnamed: C172.2, R204.2, U45.8
unnamed: C180.1, F12.1, JP100.VBUS
unnamed: C176.1, JP100.D-, R209.1
unnamed: C175.1, JP100.D+, R208.1
unnamed: R209.2, U47.12
unnamed: R208.2, U47.11
unnamed: R210.2, U47.20
unnamed: Q47.1, U45.2
unnamed: R213.1, R214.2, U45.4
unnamed: C177.2, U45.6
unnamed: J56.2, J57.2
unnamed: J56.1, J58.1
unnamed: J57.1, J59.1
unnamed: J60.1, JP108.1
unnamed: JP108.3, U45.16
unnamed: R211.2, U47.4
unnamed: Q48.2, R215.1, U47.1
RIPUP@: L1.2, Q3.3, R16.2, U1.3
RIPUP@1: L2.2, Q7.3, R33.2, U2.3
RIPUP@2: L3.2, Q11.3, R51.2, U9.3
RIPUP@3: L4.2, Q15.3, R69.2, U13.3
RIPUP@4: L5.2, Q19.3, R87.2, U17.3
RIPUP@5: L6.2, Q23.3, R105.2, U21.3
RIPUP@6: L7.2, Q27.3, R123.2, U25.3
RIPUP@7: L8.2, Q31.3, R141.2, U29.3
RIPUP@8: L9.2, Q35.3, R159.2, U33.3
RIPUP@9: L10.2, Q39.3, R177.2, U37.3
RIPUP@10: L11.2, Q43.3, R195.2, U41.3
RIPUP@11: L12.2, Q47.3, R213.2, U45.3
RST: C1.2, JP5.5, R2.1, S2.3, U4.29
RST1: C17.2, JP10.5, R19.1, S1.3, U8.29
RST2: C32.2, JP20.5, R37.1, S3.3, U12.29
RST3: C47.2, JP29.5, R55.1, S4.3, U16.29
RST4: C62.2, JP38.5, R73.1, S5.3, U20.29
RST5: C77.2, JP47.5, R91.1, S6.3, U24.29
RST6: C92.2, JP56.5, R109.1, S7.3, U28.29
RST7: C107.2, JP65.5, R127.1, S8.3, U32.29
RST8: C122.2, JP74.5, R145.1, S9.3, U36.29
RST9: C137.2, JP83.5, R163.1, S10.3, U40.29
RST10: C152.2, JP92.5, R181.1, S11.3, U44.29
RST11: C167.2, JP101.5, R199.1, S12.3, U48.29
RXD: JP9.TXO, R11.1, U4.30
RXD1: JP14.TXO, R30.1, U8.30
RXD2: JP23.TXO, R48.1, U12.30
RXD3: JP32.TXO, R66.1, U16.30
RXD4: JP41.TXO, R84.1, U20.30
RXD5: JP50.TXO, R102.1, U24.30
RXD6: JP59.TXO, R120.1, U28.30
RXD7: JP68.TXO, R138.1, U32.30
RXD8: JP77.TXO, R156.1, U36.30
RXD9: JP86.TXO, R174.1, U40.30
RXD10: JP95.TXO, R192.1, U44.30
RXD11: JP104.TXO, R210.1, U48.30
RXLED: D1.C, U6.17
RXLED1: D4.C, U7.17
RXLED2: D7.C, U11.17
RXLED3: D10.C, U15.17
RXLED4: D13.C, U19.17
RXLED5: D16.C, U23.17
RXLED6: D19.C, U27.17
RXLED7: D22.C, U31.17
RXLED8: D25.C, U35.17
RXLED9: D28.C, U39.17
RXLED10: D31.C, U43.17
RXLED11: D34.C, U47.17
SCL: Q2.3, U4.28
SCL1: Q6.3, U8.28
SCL2: Q10.3, U12.28
SCL3: Q14.3, U16.28
SCL4: Q18.3, U20.28
SCL5: Q22.3, U24.28
SCL6: Q26.3, U28.28
SCL7: Q30.3, U32.28
SCL8: Q34.3, U36.28
SCL9: Q38.3, U40.28
SCL10: Q42.3, U44.28
SCL11: Q46.3, U48.28
SDA: Q1.3, U4.27
SDA1: Q5.3, U8.27
SDA2: Q9.3, U12.27
SDA3: Q13.3, U16.27
SDA4: Q17.3, U20.27
SDA5: Q21.3, U24.27
SDA6: Q25.3, U28.27
SDA7: Q29.3, U32.27
SDA8: Q33.3, U36.27
SDA9: Q37.3, U40.27
SDA10: Q41.3, U44.27
SDA11: Q45.3, U48.27
TEMP_DAT: JP1.2, JP4.2, R14.1, U4.2
TEMP_DAT1: JP12.2, JP15.2, R32.1, U8.2
TEMP_DAT2: JP21.2, JP24.2, R50.1, U12.2
TEMP_DAT3: JP30.2, JP33.2, R68.1, U16.2
TEMP_DAT4: JP39.2, JP42.2, R86.1, U20.2
TEMP_DAT5: JP48.2, JP51.2, R104.1, U24.2
TEMP_DAT6: JP57.2, JP60.2, R122.1, U28.2
TEMP_DAT7: JP66.2, JP69.2, R140.1, U32.2
TEMP_DAT8: JP75.2, JP78.2, R158.1, U36.2
TEMP_DAT9: JP84.2, JP87.2, R176.1, U40.2
TEMP_DAT10: JP93.2, JP96.2, R194.1, U44.2
TEMP_DAT11: JP102.2, JP105.2, R212.1, U48.2
TXD: JP9.RXI, R12.1, U4.31
TXD1: JP14.RXI, R31.1, U8.31
TXD2: JP23.RXI, R49.1, U12.31
TXD3: JP32.RXI, R67.1, U16.31
TXD4: JP41.RXI, R85.1, U20.31
TXD5: JP50.RXI, R103.1, U24.31
TXD6: JP59.RXI, R121.1, U28.31
TXD7: JP68.RXI, R139.1, U32.31
TXD8: JP77.RXI, R157.1, U36.31
TXD9: JP86.RXI, R175.1, U40.31
TXD10: JP95.RXI, R193.1, U44.31
TXD11: JP104.RXI, R211.1, U48.31
TXLED: D2.C, U6.10
TXLED1: D5.C, U7.10
TXLED2: D8.C, U11.10
TXLED3: D11.C, U15.10
TXLED4: D14.C, U19.10
TXLED5: D17.C, U23.10
TXLED6: D20.C, U27.10
TXLED7: D23.C, U31.10
TXLED8: D26.C, U35.10
TXLED9: D29.C, U39.10
TXLED10: D32.C, U43.10
TXLED11: D35.C, U47.10

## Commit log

2014-12-20 :space_invader: Added .gitattributes & .gitignore files
2014-12-20 Initial commit
    Firmware is mostly done. Hardware is mostly done.
2014-12-23 Small fixes to pass initial QC checklist
2014-12-23 Fixing file locations.
2014-12-23 Added external serial connection.
    Can be used to emergency reset the serial interface back to 9600bps.
2014-12-30 First round of fixes from PLewis review
    Fixed J1/J3 labels on schematic. Fixed LED colors to match standards.
    Added test point for VCC. Improved layout around TMP102. Added measures.
2014-12-30 Fixing issue #1
2015-01-15 Update file names. Remove stat LED blink delay.
2015-02-05 Lots of changes. v02 ready for proto.
    Changed to RJ45, FTDI connection, MOSFETs to temp sensor, silk, shutdown
    from temp sensor to ATmega.
2015-02-05 Silk fix. Dim fix. Reroute traces to TMP102.
2015-02-06 Bumped RJ45 to fix issue #3
2015-03-23 Adding support for temperature readings.
2015-04-09 Remove v-reg add PNP for internal v-reg.
    Added 4.7k pull up for One Wire external temp.
2015-04-09 Fixed issue 4 - DRC errors and schematic markings.
2015-04-09 Crazy re-design to use screw terminals.
    Rather than RJ45 I have moved to screw terminals. This should make it
    easy on end customers who don't have a solder iron to get up and running
    immediately.
2015-04-13 New version with screw terminals. Ready for review.
2015-04-13 Silkscreen fix.
2015-10-12 Fix screw terminal spacing. Small firmware changes.
    Footprint error on the screw terminals that prevented them from being
    linked together (spaced too far apart). Should be fixed now but needs
    double checking.
2015-10-12 Adding Particle sketch
2015-10-12 Adding photos and link to project article.
2015-10-12 Adding photo to readme
2016-03-07 Adding Working Copies of New Rev
2016-03-07 Delete openScale_v04.brd
    Should not be in master
2016-03-15 Updated Board files
2016-03-15 Updated Board and Schematic
2016-03-15 Updated Board and Schematic after reviewing QC checklist
2016-03-15 Updated Board file
2016-03-29 Updated Board and Schematic files per QC checklist
2016-03-29 Updated yellow LED
2016-05-02 Updated Board and Schemtic
2016-05-03 Updated silk on brd file
2016-05-06 Adding power savings to main firmware
    If unit is in trigger mode it will now shut down to about 4mA in sleep
    mode. It wakes up when a character is received. Removing extra testing
    sketches.
2016-05-06 Added ability to set the character that triggers a reading
    Rather than trigger off any serial char this allows user to set the char
    to trigger on. This is helpful when OpenScale is connected to a serial
    bus and other debug messages are being sent.
2016-05-09 Updated BRD and SCH file per Engineering Design Review
2016-05-11 Updated Brd and Sch files per QC review.
2016-05-11 Changed silk: Centered bottom layer text on FTDI headers
2016-05-24 Renaming Files
2016-05-24 adding header files for each sketch
2016-06-01 created panel v10
2016-07-12 Updated OpenScale with Power Reduction and Trigger Character
2016-07-15 removed tmp102 silk from panel v10
2016-12-01 Value Additions to .brd and .sch for 3D Model
2017-01-23 Updated firmware (Tare-fix)
2017-01-26 Updated firmware -- Calibrated Tare will now save in EEPROM after power cycle
2017-01-26 Updated firmware -- Calibrated tare point will be saved to EEPROM after power cycle
2017-01-26 Updated Firmware -- Calibrated Tare Point will be saved in EEPROM after power cycle
2017-02-08 define LOCATION_TRIGGER_CHARACTER EEPROM address
2017-02-08 set tare point and calibration fac after loading vals on startup
2017-02-13 Updating Firmware
2018-11-04 Update readme. Remove old varience ino.
2018-11-04 Whitespace fix
2018-11-06 Beginning v12 scope of work
2018-11-06 New calibration works
2018-11-06 Re-arrange how cal settings are shown
2018-11-06 Broke the spagetti code into individual tabs
2018-11-06 Move systemHeader to tab
2018-11-06 Temp removed scale power cycling. Fixed double menu issue.
2018-11-06 Set remote temp to off by default
2018-11-06 Default EEPROM settings now load correctly
    The boolean variables were coming in as not > 1, so they were defaulting to 255. By casting these settings as bytes, they test correctly. Might have been a compiler change in Arduino? Or it never pro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
2018-11-06 Remove duplicate tare point code
    Both methods produced the same tare point (within 0.01%)
2018-11-06 Set report time now uses easier text input method
2018-11-06 Change average amt and decimals to text input
2018-11-06 Calibration now echos user's input
2018-11-06 Removed scale power cycling. Maintained ATmega sleep.
    Power cycle the HX711 was causing a reading to be dropped every once and awhile causing the calibration routine and general reading to fail. Works now, but at the expense of ~1.5mA additional.
2018-11-06 Removing extraneous sub directory
2018-11-06 Fixed the set_default_settings settings.
2019-02-26 Changed HX711 start up to match lib changes
2019-05-15 Update SparkFun_openScale.sch
    Updating AVDD equation to be correct
